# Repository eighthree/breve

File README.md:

# breve
E73-2G4M04S Module breakout board
NRF52832 SoC

# module / datasheet
http://www.cdebyte.com/en/product-view-news.aspx?id=243
http://www.cdebyte.com/en/downpdf.aspx?id=243

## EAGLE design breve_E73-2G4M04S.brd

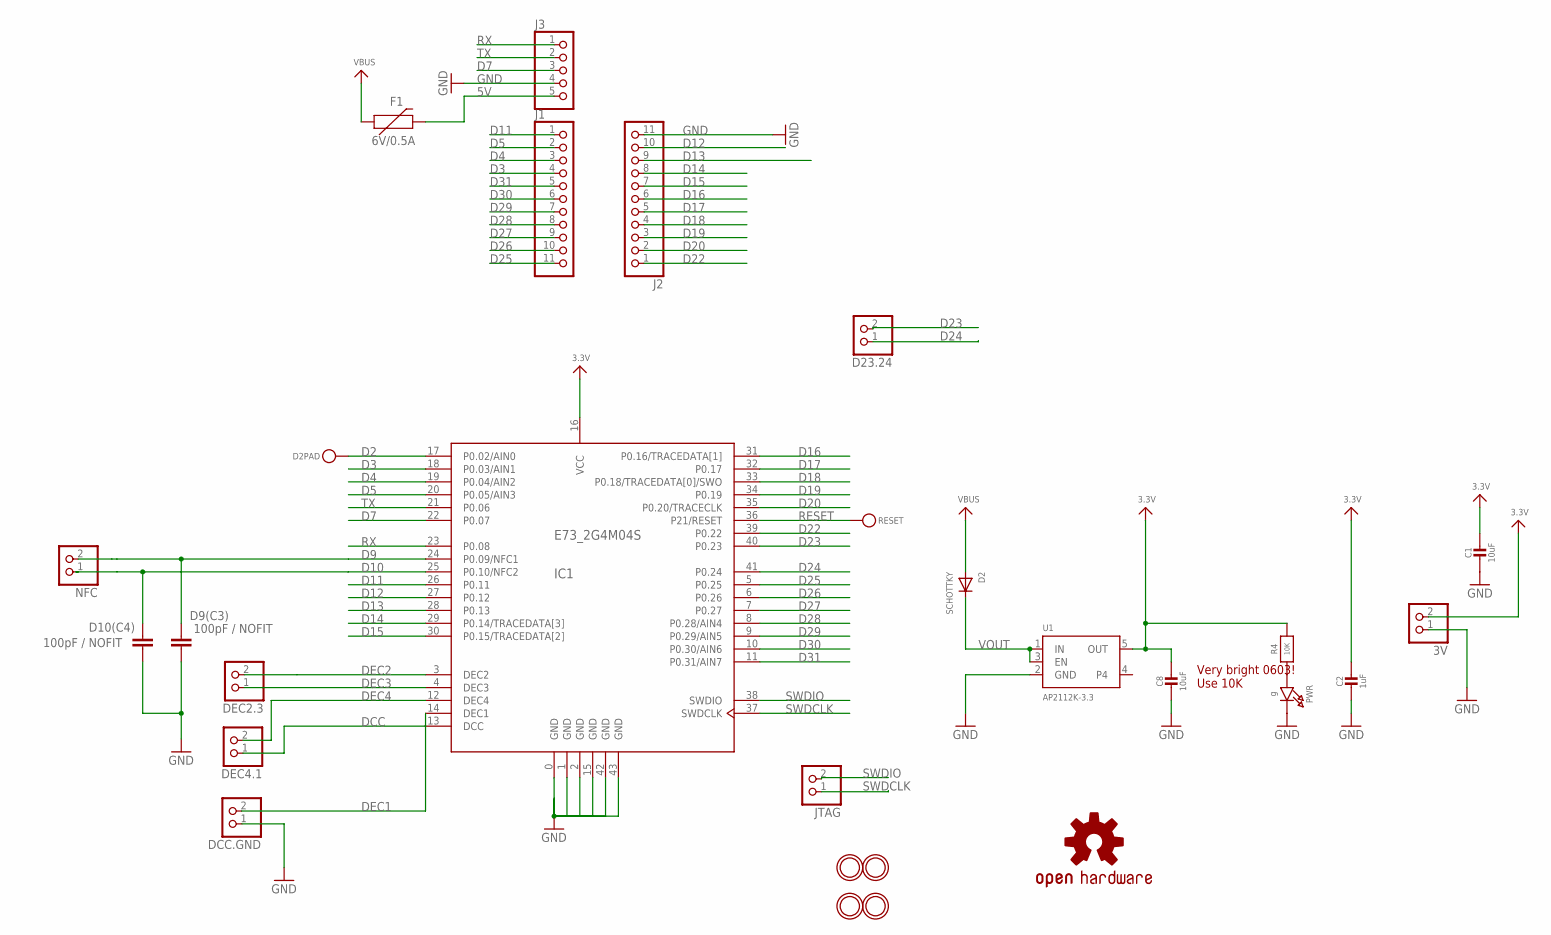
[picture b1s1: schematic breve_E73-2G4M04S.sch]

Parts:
3V: HEADER-1X2ROUND; 1X02_ROUND
C1, C8: 10uF; 0805-NO
C2: 1uF; 0603-NO
D2: SCHOTTKY; SOD-123FL
D2PAD: TESTPOINTROUND1.5MM; TESTPOINT_ROUND_1.5MM
D9(C3), D10(C4): 100pF / NOFIT; C0603
D23.24: HEADER-1X2ROUND; 1X02_ROUND
DCC.GND: HEADER-1X2ROUND; 1X02_ROUND
DEC2.3, DEC4.1: HEADER-1X2ROUND; 1X02_ROUND
F1: 6V/0.5A; 1206
IC1: E73_2G4M04S
J1, J2: PINHD-1X11_2.54-SX; 1X11-SX
J3: PINHD-1X05_2.54-SX; 1X05-SX
JTAG: HEADER-1X2ROUND; 1X02_ROUND
LOGO4: OSHW-LOGOS; OSHW-LOGO-S
NFC: HEADER-1X2ROUND; 1X02_ROUND
PWR: g; CHIPLED_0603_NOOUTLINE
R4: 10K; 0603-NO
RESET: TESTPOINTROUND1.5MM; TESTPOINT_ROUND_1.5MM
U1: AP2112K-3.3; SOT23-5
U$2, U$6, U$31, U$32: MOUNTINGHOLE2.5; MOUNTINGHOLE_2.5_PLATED

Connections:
3.3V: 3V.2, C1.1, C2.1, C8.1, IC1.16 (VCC), R4.2, U1.5 (OUT)
5V: F1.2, J3.5
D2: D2PAD.P$1, IC1.17 (P0.02/AIN0)
D3: IC1.18 (P0.03/AIN1), J1.4
D4: IC1.19 (P0.04/AIN2), J1.3
D5: IC1.20 (P0.05/AIN3), J1.2
D7: IC1.22 (P0.07), J3.3
D9: D9(C3).2, IC1.24 (P0.09/NFC1), NFC.2
D10: D10(C4).2, IC1.25 (P0.10/NFC2), NFC.1
D11: IC1.26 (P0.11), J1.1
D12: IC1.27 (P0.12), J2.10
D13: IC1.28 (P0.13), J2.9
D14: IC1.29 (P0.14/TRACEDATA[3]), J2.8
D15: IC1.30 (P0.15/TRACEDATA[2]), J2.7
D16: IC1.31 (P0.16/TRACEDATA[1]), J2.6
D17: IC1.32 (P0.17), J2.5
D18: IC1.33 (P0.18/TRACEDATA[0]/SWO), J2.4
D19: IC1.34 (P0.19), J2.3
D20: IC1.35 (P0.20/TRACECLK), J2.2
D22: IC1.39 (P0.22), J2.1
D23: D23.24.2, IC1.40 (P0.23)
D24: D23.24.1, IC1.41 (P0.24)
D25: IC1.5 (P0.25), J1.11
D26: IC1.6 (P0.26), J1.10
D27: IC1.7 (P0.27), J1.9
D28: IC1.8 (P0.28/AIN4), J1.8
D29: IC1.9 (P0.29/AIN5), J1.7
D30: IC1.10 (P0.30/AIN6), J1.6
D31: IC1.11 (P0.31/AIN7), J1.5
DCC: DEC4.1.1, IC1.13 (DCC)
DEC1: DCC.GND.2, IC1.14 (DEC1)
DEC2: DEC2.3.2, IC1.3 (DEC2)
DEC3: DEC2.3.1, IC1.4 (DEC3)
DEC4: DEC4.1.2, IC1.12 (DEC4)
GND: 3V.1, C1.2, C2.2, C8.2, D9(C3).1, D10(C4).1, DCC.GND.1, IC1.0 (GND), IC1.1 (GND), IC1.2 (GND), IC1.15 (GND), IC1.42 (GND), IC1.43 (GND), J2.11, J3.4, PWR.C, U1.2 (GND)
unnamed: PWR.A, R4.1
RESET: IC1.36 (P21/RESET), RESET.P$1
RX: IC1.23 (P0.08), J3.1
SWDCLK: IC1.37 (SWDCLK), JTAG.1
SWDIO: IC1.38 (SWDIO), JTAG.2
TX: IC1.21 (P0.06), J3.2
VBUS: D2.A, F1.1
VOUT: D2.C, U1.1 (IN), U1.3 (EN)

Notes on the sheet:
Very bright 0603! Use 10K

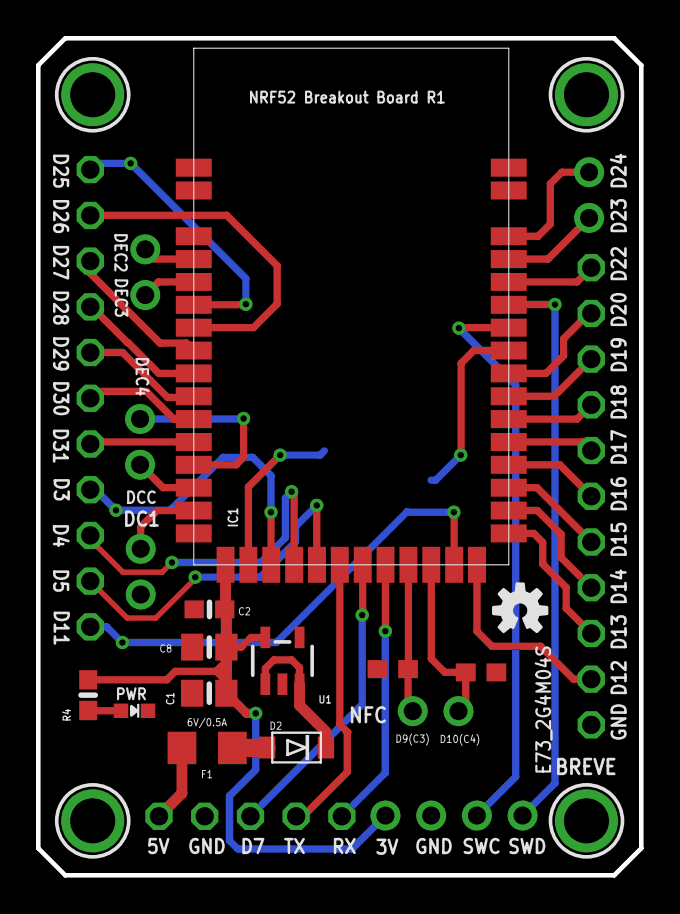
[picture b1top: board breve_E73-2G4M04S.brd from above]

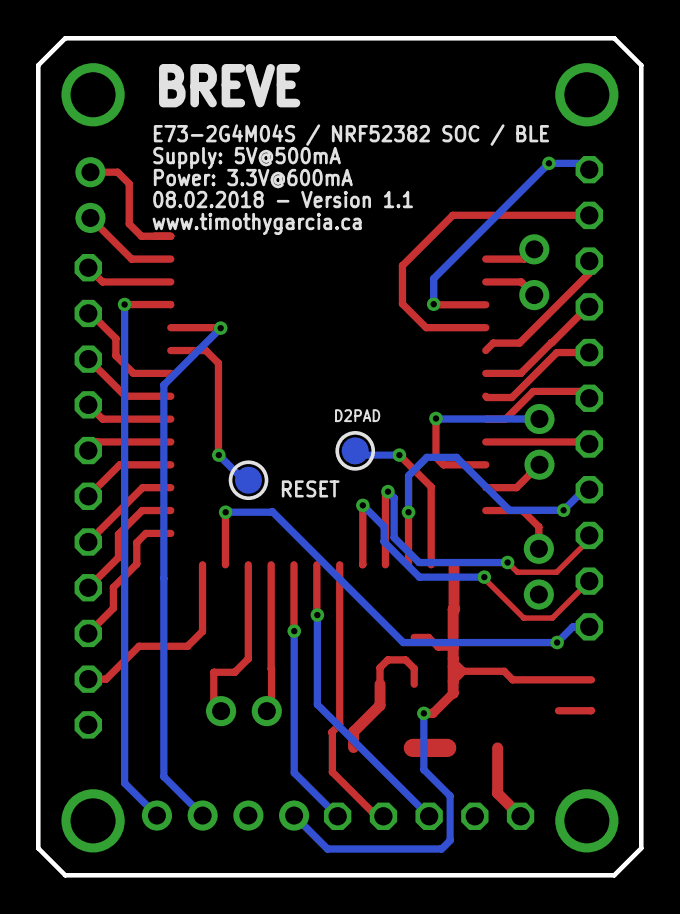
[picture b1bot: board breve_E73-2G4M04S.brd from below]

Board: 2 copper layers, 33.5 x 46.5 mm, 28 parts (2 on the bottom side), 43 nets.

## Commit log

2018-08-02 E73-2G4M04S breakout board
    * Pins to match MDBT42Q Breakout
    * 500mA polyfuse
    * AP2112K-3.3 Regulator
2018-10-09 Update LICENSE

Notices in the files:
parts and their libraries:
microbuilder: This work is placed in the public domain, and may be freely used for commercial and non-commercial work with the following conditions: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
SparkFun-Aesthetics: Licensing: Creative Commons ShareAlike 4.0 International - https://creativecommons.org/licenses/by-sa/4.0
